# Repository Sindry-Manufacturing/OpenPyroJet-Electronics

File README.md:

# OpenPyroJet-Electronics

Software licensed under: AGPL-3

Hardware licensed under: CERN-OHL-S-V2

These sets of sub-folders contain KiCAD 5.1 based designs for experimenting with a PCB based metal/ceramic 3D Printer. 

Gen3.1_Printhead       ; initial experimental PCB based Printhead

Printhead-Controller   ; HW board that runs the Driver board

Printhead-Driver       ; HW circuitry to drive the printhead

software               ; basic Arduino based software to test the Controller & Driver boards.  See: https://github.com/Sindry-Manufacturing/OpenPyrojet-Jetpack  for a much more complete solution

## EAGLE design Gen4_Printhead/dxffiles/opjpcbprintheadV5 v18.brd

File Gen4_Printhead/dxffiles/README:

this is where the 2D CAD files of the gen4 printhead are stored.
Board files, dxfs etc.

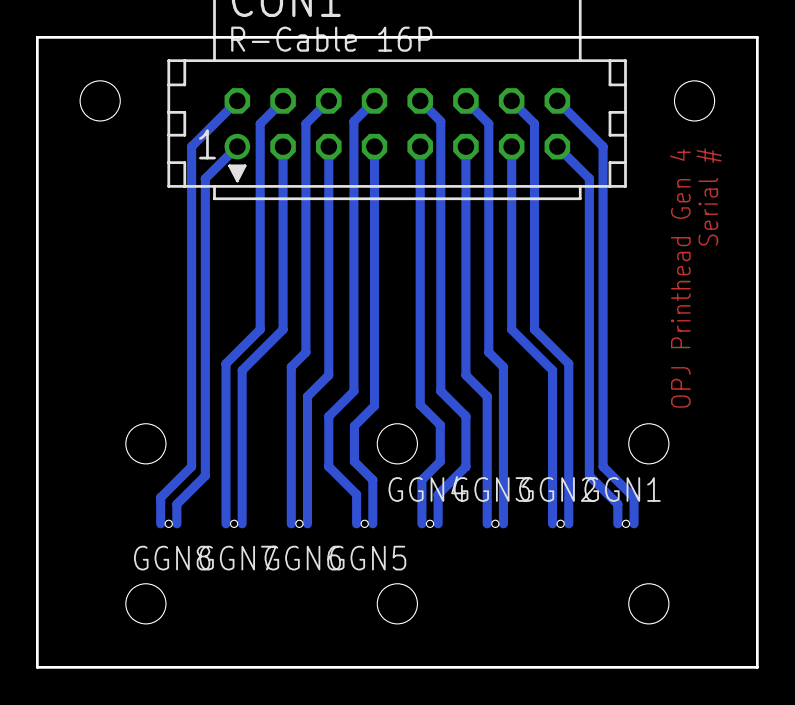
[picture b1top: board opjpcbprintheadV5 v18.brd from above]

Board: 2 copper layers, 40.0 x 35.0 mm, 9 parts (0 on the bottom side), 16 nets.

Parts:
CON1: CON16
GGN1, GGN2, GGN3, GGN4, GGN5, GGN6, GGN7, GGN8: OPJGASGUN

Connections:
unnamed: CON1.1, GGN8.VCC
unnamed: CON1.3, GGN7.VCC
unnamed: CON1.5, GGN6.VCC
unnamed: CON1.7, GGN5.VCC
unnamed: CON1.9, GGN4.VCC
unnamed: CON1.11, GGN3.VCC
unnamed: CON1.13, GGN2.VCC
unnamed: CON1.15, GGN1.VCC
unnamed: CON1.16, GGN1.GND
unnamed: CON1.2, GGN8.GND
unnamed: CON1.4, GGN7.GND
unnamed: CON1.6, GGN6.GND
unnamed: CON1.8, GGN5.GND
unnamed: CON1.14, GGN2.GND
unnamed: CON1.12, GGN3.GND
unnamed: CON1.10, GGN4.GND

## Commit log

2022-03-18 initial import of Controller and Driver PCB KiCAD 5.1 designs
2022-03-22 final PCB KiCAD design files for V0.5 as sent off for manufacture at JLCPCB 2022-03-22
2022-03-27 Adding in the Gen3.1 printhead KiCAD PCB design files
2022-03-27 adding in Printhead schematic diagram
2022-03-29 adding in Gen3.1a Conector PCB inlet modifications - hole reduced from 1.27mm to 1mm, or 0.8mm
2022-03-29 updated Printhead to Gen3.1b - Nozzle screw holes swapped from 1.27mm to 0.635mm. Added labels to each board to help with identification
2022-04-03 Repo now has an updated panel with 3mm holes in top plate. Each layer is alphabet coded.
2022-04-26 Adding in PCB testing software
2022-04-26 adding in explination doc
2022-04-26 adding PCB stencil files and updated BOM listings that include LCSC part nnumbers
2022-05-11 Updating Controller and Driver boards to version 0.6
2022-05-11 adding in ESP32 DAC to ADC121 check/test
2022-05-11 adding in test result chart
2022-05-11 updated Controller Test code
2022-05-12 Updated BOM spreadsheets with LCSC partnumbers. Changed schematic and voltage divider values
2022-06-10 adding in test code of V0.6 PCB
2022-06-11 fixes for VSW voltage readings
2022-06-14 Adding in version 0.7 KiACD design files
2022-06-14 changes to make Rotary Encoder work better. Still configured for VSW monitoring
2023-02-08 added fusion archive files
    Added the complete base design files from fusion 360 and eaglePCB to allow editing and modification of the underlying design.
2023-07-11 Update README.md
    added license text.
2023-07-11 Add files via upload
    Added CERN OHL-S-V2
2023-07-11 Create LICENSE
    added a proper detectable license template for included software.
